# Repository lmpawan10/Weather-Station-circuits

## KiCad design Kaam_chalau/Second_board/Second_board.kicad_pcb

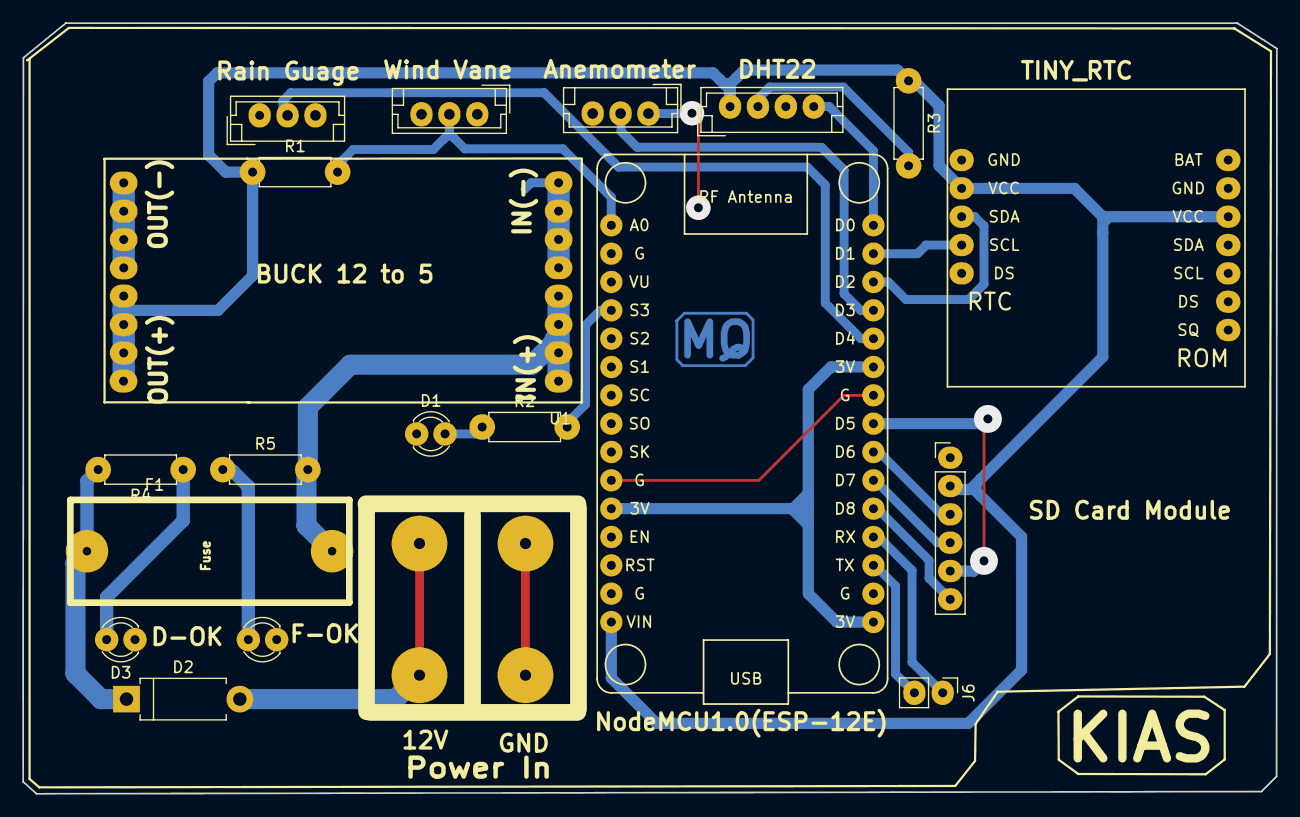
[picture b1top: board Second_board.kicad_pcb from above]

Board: 2 copper layers, 112.4 x 69.1 mm, 11 parts (0 on the bottom side), 6 nets.

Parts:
D1, D3: LED; LED_D3.0mm
D2: D; Diode_Small
F1: Fuse; Fuse_Holder
J6: Conn_01x02_Female; PinHeader_1x02_P2.54mm_Vertical
R1, R3: 10k; Resistor_small
R2, R4, R5: R; Resistor_small
U1: Buck; Buck_Regulator

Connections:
/Vin(5V): R1.1, R3.1, U1.3
GND: D1.1, D3.1, U1.2, U1.4
unnamed: D1.2, R2.1
unnamed: D2.1, F1.2, R4.2
unnamed: D3.2, R4.1
unnamed: F1.1, R5.2, U1.1

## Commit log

2021-07-16 All circuits added
2021-07-16 Libraries and footprints added
2021-08-07 HD-W60 datasheet added
